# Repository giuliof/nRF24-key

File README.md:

# nRF key

Interface for Nordic nRF24L01 wireless modules.

## Project structure

In this repository you can find:
```
nRF-key
 |__ schematics --> KiCAD schematic
 |__ code       --> source code for ATtiny2313 microcontroller
```

## BOM

|Designator    | Description                | MPN               |
|--------------|----------------------------|-------------------|
|C2 C7 C8 C10  | capacitor 100n 0805        | 0805F104M500NT    |
|C9            | capacitor tantalum 10u     | TAJA106K016RNJ    |
|C5 C6         | capacitor 22p 0805         | 0805N220J500CT    |
|D1 D2 D3      | red led 0805               | QBLP631-R         |
|R1 R5         | resistor 10k 0805          | RC0805JR-0710KL   |
|R2 R3 R4      | Resistor 330 0805          | 0805W8J0331T5E    |
|U2            | microcontroller ATtiny2313 | ATTINY2313A-SU    |
|U1            | usb ttl uart ch340c        | CH340C            |
|U3            | LDO voltage regulator 3v3  | MCP1700T-3302E/TT |
|Y1            | crystal 8M                 | 1C208000BC0R      |

## Code features

Communication with nRF key is via 9600baud 8N1 serial port. Data received from another module is printed. Data to send is packaged in a 32byte maximum structure and must be followed by CR. Bytes over 32 (except for CR) will be ignored.
This is not a transparent bridge, but can be easily implemented.

nRF24L01 registers (i.e. tx/rx addresses) can be reprogrammed pressing programming button (i.e. holding low BTN/PD4 line) while inserting key. Programming mode is selected (both TX_LED and RX_LED will turn on), next 32byte will be stored in settings EEPROM. Data is structured as following:

| Byte n. |                       Function                  |  nRF reg. |
|---------|-------------------------------------------------|-----------|
|    0    |Configure register                               |     0     |
|    1    |Enable automatic answer function                 |     1     |
|    2    |Enable receive address                           |     2     |
|    3    |Setup address width                              |     3     |
|    4    |Automatic retransmission                         |     4     |
|    5    |Set channel frequency                            |     5     |
|    6    |Set transmission rate, LNA gain, transmit power  |     6     |
| 7&div;11|RX address for data channel 0                    |     10    |
|12&div;16|RX address for data channel 1                    |     11    |
|   17    |RX address for data channel 2                    |     12    |
|   18    |RX address for data channel 3                    |     13    |
|   19    |RX address for data channel 4                    |     14    |
|   20    |RX address for data channel 5                    |     15    |
|21&div;25|TX address                                       |     16    |
|   26    |RX data for channel 0                            |     17    |
|   27    |RX data for channel 1                            |     18    |
|   28    |RX data for channel 2                            |     19    |
|   29    |RX data for channel 3                            |     20    |
|   30    |RX data for channel 4                            |     21    |
|   31    |RX data for channel 5                            |     22    |

## How To

1. Make the PCB and solde it (I have a protoboard version too);
2. Obtain an AVR programmer (usbasp or Arduino as ISP)
3. Compile the code:
 * install `gcc-avr` `avr-libc` `avrdude`;
 * move in code directory;
 * type `make`;
 * check in Makefile if the programmer is correct;
 * type `make eeprom` then `make flash`.

## Authors

* **Giulio Fieramosca** - [giuliof](https://github.com/giuliof)

## License

This project is released under the MIT License - see the [LICENSE.md](LICENSE.md) file for details

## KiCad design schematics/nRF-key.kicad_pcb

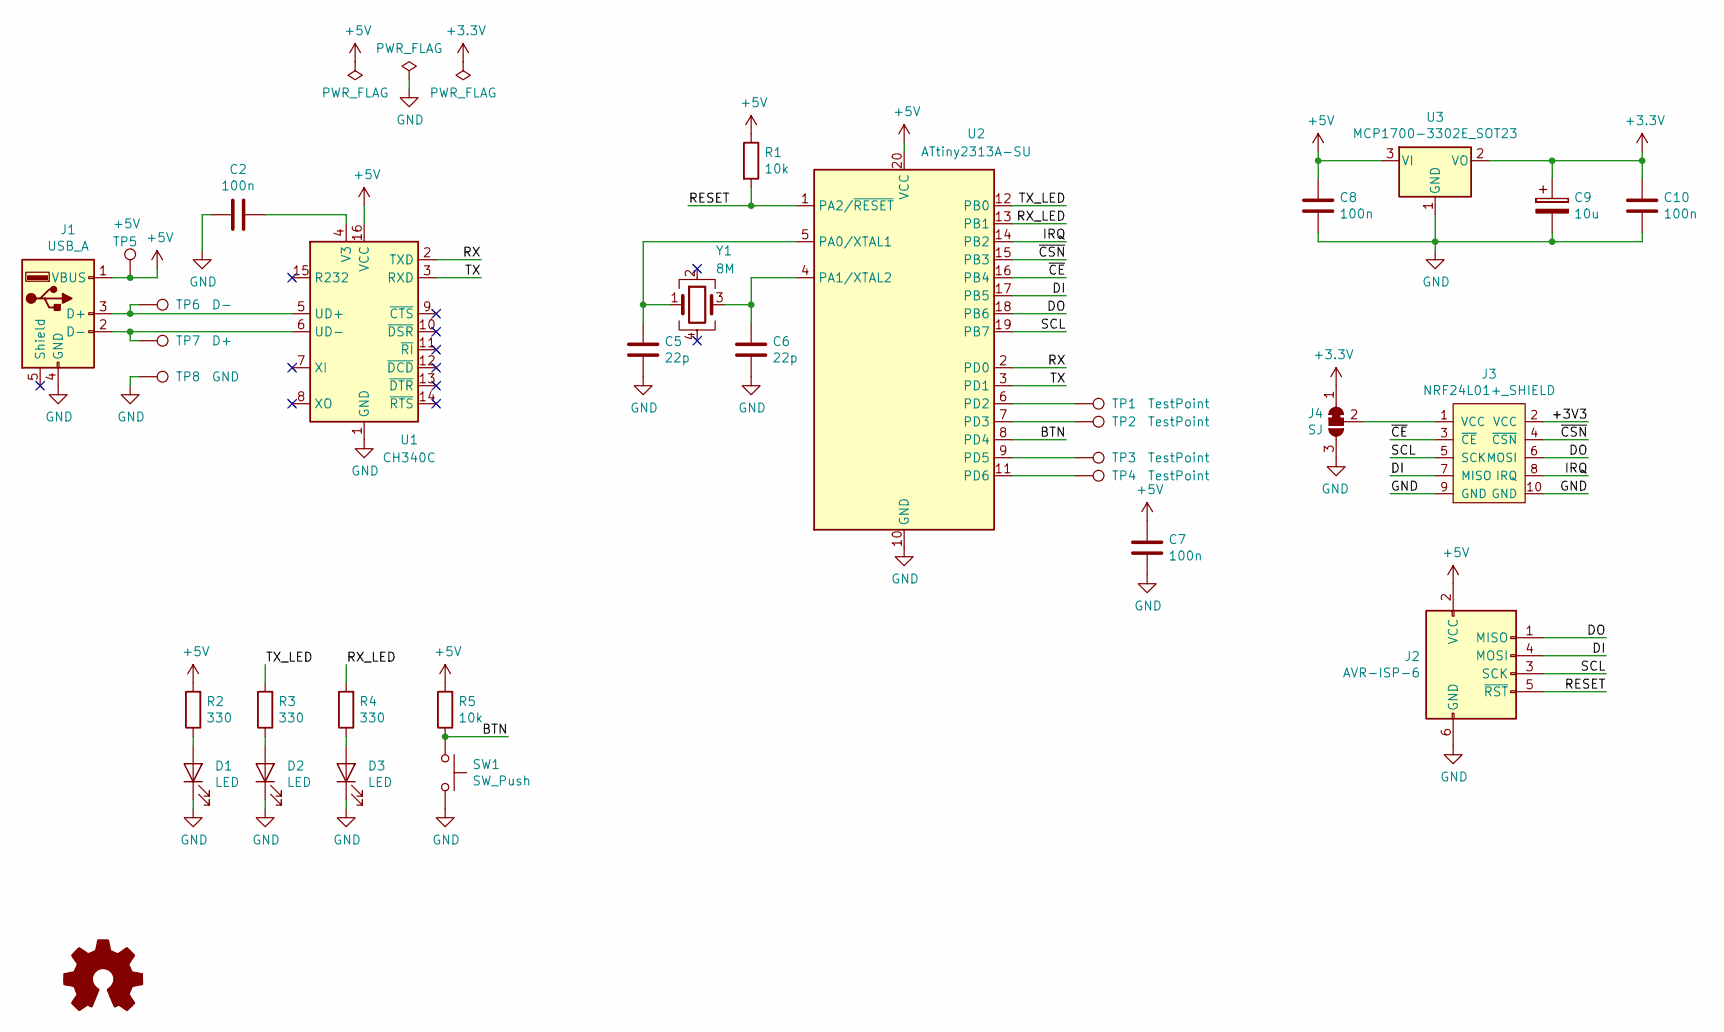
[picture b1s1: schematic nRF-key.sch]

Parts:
C2, C7, C8, C10: 100n; C_0805_2012Metric; Part no 0805F104M500NT
C5, C6: 22p; C_0805_2012Metric; Part no 0805N220J500CT
C9: 10u; CP_EIA-3216-12_Kemet-S; Part no TAJA106K016RNJ
D1, D2, D3: LED; LED_0805_2012Metric; Part no QBLP631-R
J1: USB_A; usb-PCB
J2: AVR-ISP-6; PogoPins-2x03-ICSP
J3: NRF24L01+_SHIELD; nRF24-2x05_P2.54mm
J4: SJ; SolderJumper-3_P1.3mm_Open_RoundedPad1.0x1.5mm
LOGO1: Logo_Open_Hardware_Small; oshw-logo-10mm
R1, R5: 10k; R_0805_2012Metric; Part no RC0805JR-0710KL
R2, R3, R4: 330; R_0805_2012Metric; Part no 0805W8J0331T5E
SW1: SW_Push; _PTS525SK15-SMT-Pushbutton
TP1, TP2, TP3, TP4: TestPoint; TestPoint_THTPad_D1.0mm_Drill0.5mm
TP5: +5V; TestPoint_THTPad_D1.0mm_Drill0.5mm
TP6: D-; TestPoint_THTPad_D1.0mm_Drill0.5mm
TP7: D+; TestPoint_THTPad_D1.0mm_Drill0.5mm
TP8: GND; TestPoint_THTPad_D1.0mm_Drill0.5mm
U1: CH340C; SOIC-16_3.9x9.9mm_P1.27mm; Part no CH340C
U2: ATtiny2313A-SU; SOIC-20W_7.5x12.8mm_P1.27mm; Part no ATTINY2313A-SU
U3: MCP1700-3302E_SOT23; SOT-23; Part no MCP1700T-3302E/TT
Y1: 8M; Crystal_SMD_3225-4Pin_3.2x2.5mm; Part no 1C208000BC0R

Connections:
+5V: C7.1, C8.1, J1.1 (VBUS), J2.2 (VCC), R1.1, R2.2, R5.2, TP5.1, U1.16 (VCC), U2.20 (VCC), U3.3 (VI)
/BTN: R5.1, SW1.1, U2.8 (PD4)
/DI: J2.4 (MOSI), J3.7 (MISO), U2.17 (PB5)
/DO: J2.1 (MISO), J3.6 (MOSI), U2.18 (PB6)
/IRQ: J3.8 (IRQ), U2.14 (PB2)
/RESET: J2.5 (~RST), R1.2, U2.1 (PA2/~RESET)
/RX: U1.2 (TXD), U2.2 (PD0)
/RX_LED: R4.2, U2.13 (PB1)
/SCL: J2.3 (SCK), J3.5 (SCK), U2.19 (PB7)
/TX: U1.3 (RXD), U2.3 (PD1)
/TX_LED: R3.2, U2.12 (PB0)
/~CE~: J3.3 (~CE~), U2.16 (PB4)
/~CSN~: J3.4 (~CSN~), U2.15 (PB3)
GND: C2.2, C5.2, C6.2, C7.2, C8.2, C9.2, C10.2, D1.1 (K), D2.1 (K), D3.1 (K), J1.4 (GND), J2.6 (GND), J3.9 (GND), J3.10 (GND), J4.3 (B), SW1.2, TP8.1, U1.1 (GND), U2.10 (GND), U3.1 (GND)
unnamed: C2.1, U1.4 (V3)
unnamed: C5.1, U2.5 (PA0/XTAL1), Y1.1
unnamed: C6.1, U2.4 (PA1/XTAL2), Y1.3
unnamed: D1.2 (A), R2.1
unnamed: D2.2 (A), R3.1
unnamed: D3.2 (A), R4.1
unnamed: J1.2 (D-), TP7.1, U1.6 (UD-)
unnamed: J1.3 (D+), TP6.1, U1.5 (UD+)
unnamed: J3.1 (VCC), J4.2 (C)
unnamed: TP1.1, U2.6 (PD2)
unnamed: TP2.1, U2.7 (PD3)
unnamed: TP3.1, U2.9 (PD5)
unnamed: TP4.1, U2.11 (PD6)

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
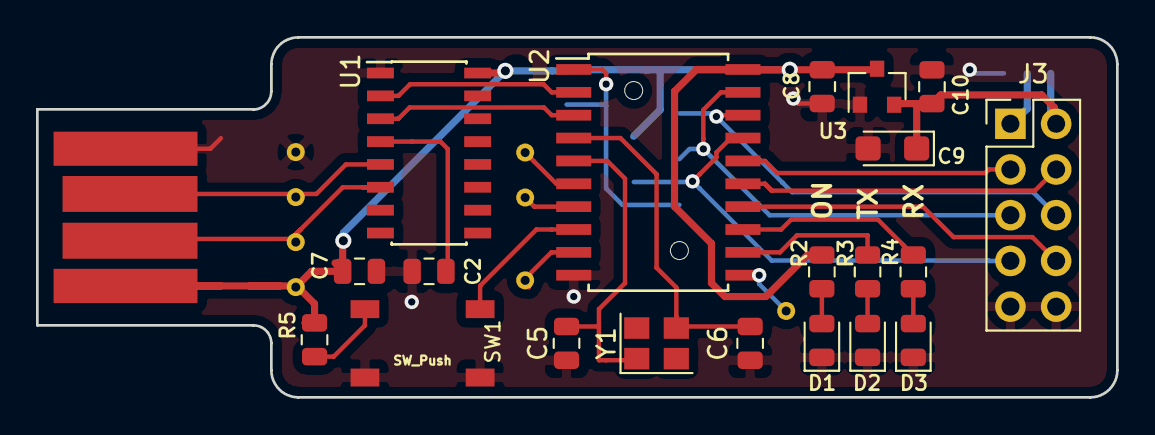
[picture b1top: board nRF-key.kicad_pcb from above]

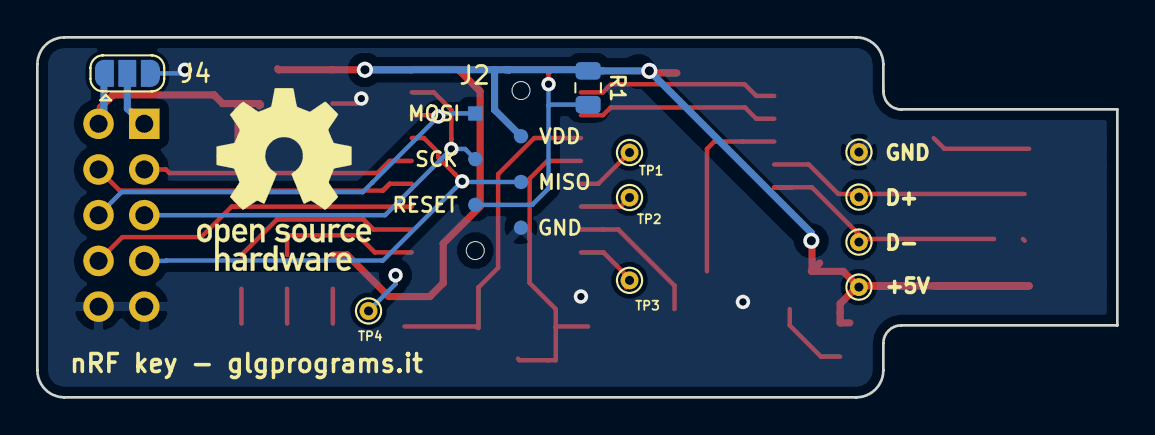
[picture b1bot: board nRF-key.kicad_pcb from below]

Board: 2 copper layers, 60.0 x 20.0 mm, 33 parts (12 on the bottom side), 28 nets.

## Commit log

2019-06-23 [docs] typo in readme
